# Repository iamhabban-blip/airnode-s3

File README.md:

# AirNode S3 — ESP32-S3 Environmental Sensor Node

A compact, USB-C powered Wi-Fi/BLE sensor board: ESP32-S3 module, Bosch BME280 (temperature / humidity / pressure), a Qwiic/STEMMA-QT port for more I2C sensors, a UART debug header and a 6-GPIO breakout.

Designed in **KiCad 7** as a native, self-contained project (local symbol, footprint and 3D libraries), with fabrication and assembly data ready for JLCPCB-class manufacturing.

**Status:** design complete and verified (ERC + DRC clean). Not yet fabricated.

| | |
|---|---|
| Board | 44 × 54 mm, 2 layers, 1.6 mm FR-4, 1 oz copper, 2 mm corner radius |
| Parts | 27 placed (SMD except the two pin headers and the USB-C shell legs), 4 × M2.5 mounting holes |
| Routing | 245 track segments, 120 vias, 0 unrouted |
| Rules | 0.2 mm track/space, 0.6/0.3 mm vias, 0.3 mm copper-to-edge |
| ERC | 0 errors, 0 warnings (1 reviewed exclusion, see below) |
| DRC | 0 violations, 0 unconnected, 0 footprint errors |

| Board render (top / bottom) | KiCad PCB editor |
|---|---|
|  |  |

---

## Schematic

Single A3 sheet, grouped into functional blocks (USB-C input, LDO, MCU, reset/boot, LEDs, sensor/I2C, debug/GPIO). Full PDF: [`docs/airnode-schematic.pdf`](docs/airnode-schematic.pdf).

---

## Design decisions

### 1. Power input and protection
- **USB-C sink, USB 2.0 only.** 5.1 kΩ pull-downs on CC1/CC2 (R1, R2) make the board a standard sink, so any USB-C charger or port supplies 5 V. No PD controller is needed at this power level.
- **Both D+/D− pairs connected** (A6/B6, A7/B7), so the plug works in either orientation.
- **F1, 500 mA PTC fuse** on VBUS protects the host port and the cable from a board-level short.
- **U3, USBLC6-2SC6 TVS array** sits directly behind the connector and clamps ESD on D+/D− and VBUS before it can reach the ESP32. It is placed as a flow-through (rotated 270°) so the data lines pass straight under it without stubs.

### 2. 3.3 V regulation
- **U2, AP2112K-3.3 LDO:** 600 mA output and 250 mV dropout. Wi-Fi TX bursts on the ESP32-S3 peak at roughly 350 mA, which leaves about 40 % headroom.
- An LDO was chosen over a buck converter: at 5 V in and about 100 mA average, dissipation is around 0.17 W. That is well within SOT-23-5 limits, avoids switching noise near the sensor and antenna, and costs fewer parts.
- **Capacitors:** 10 µF on the input (C1) and output (C2), then 10 µF + 100 nF (C3, C4) at the module's 3V3 pin for Wi-Fi burst current.

### 3. MCU
- **ESP32-S3-WROOM-1-N8** (8 MB flash, PCB antenna, pre-certified module).
- **Native USB** on GPIO19/20 handles both flashing and serial (CDC), so there is no USB-UART bridge chip. That saves cost, area and a failure point.
- **EN:** 10 kΩ + 1 µF RC (R3, C5) delays enable until 3V3 is stable, the reset condition Espressif recommends.
- **Strapping:** BOOT (IO0) has a 10 kΩ pull-up with a button to ground for download mode. RESET is a button on EN.
- **LEDs:** a power LED (green) and a GPIO2 status LED (blue), each with 1 kΩ (about 1.3 mA, enough for an indicator).

### 4. Sensor and I2C
- **BME280 in I2C mode:** CSB is tied high, and SDO is tied low for address 0x76.
- **I2C pull-ups:** 4.7 kΩ on SDA (IO8) and SCL (IO9), shared with the Qwiic connector in standard Qwiic pinout (GND, 3V3, SDA, SCL).
- **Thermal placement.** A board-mounted humidity/temperature sensor reads high if it sits next to heat sources. The BME280 is in the opposite bottom corner from the LDO and well below the ESP32 module.

### 5. Layout
- **Antenna.** The module sits at the top edge with its antenna flush to the board edge. The footprint's keep-out (no copper, tracks, vias or parts on either layer) covers the full width under and beside the antenna, following Espressif's guidance for a PCB-antenna module.
- **Ground strategy.** Both layers are poured with GND. The bottom layer is kept as close to a solid plane as possible: signals use it only to cross, and every SMD ground pad gets its own via to that plane. 53 stitching vias tie the two pours together on a 3 mm grid outside component courtyards.
- **USB routing.** D+ and D− run on the top layer with **zero vias** over the unbroken bottom ground plane, 29.6 mm and 30.4 mm long. At USB Full Speed (12 Mbit/s) a 0.8 mm mismatch is irrelevant; the priorities were short, via-free, referenced to ground and close-coupled.
- **USB-C pad escape.** On 16-pin USB-C the D+/D− pads interleave (D−, D+, D−, D+), so the two pairs can't both leave the pad row on one layer. D+ (A6↔B6) is joined by a short loop under the pad row and D− (B7↔A7) by a bridge above it, so both pairs exit cleanly with no vias.
- **Track widths by netclass:**
  - VBUS / VBUS_IN: 0.4 mm
  - +3V3 / GND: 0.3 mm
  - signals and USB: 0.2 mm (USB at 0.2 mm to fit the 0.5 mm-pitch connector pads)
- **Pad connections.** SMD pads connect to the pours solidly (better for reflow); through-hole pads use thermal reliefs (better for hand soldering).

*Top: the antenna keep-out band runs across the top edge, with ground pour and stitching vias everywhere else. Bottom: a near-solid ground plane under the USB and signal routing, plus header pin legends.*

### 6. Manufacturability (DFM)
- **ESP32 thermal vias opened from 0.2 to 0.3 mm.** Espressif's footprint uses 0.2 mm vias under the module's ground pad. The project's local copy uses 0.3 mm, JLCPCB's standard 2-layer minimum, so the board needs no advanced-process surcharge.
- **USB-C peg clearance.** In the GCT USB4105 land pattern, the connector's alignment-peg holes sit 0.19 mm from its outer ground pads. That is the manufacturer's geometry, so a scoped DRC rule (`airnode.kicad_dru`) relaxes hole clearance **for J1 only** rather than loosening the board-wide rule.
- **Silkscreen.**
  - Every legend stays off pads and inside the board edge.
  - Header pin names are on the bottom silkscreen, readable when the board is flipped to wire it.
  - The module's antenna-end silkscreen is pulled 0.5 mm inside its outline so it never crosses the board edge.
- **Assembly files.**
  - The BOM groups parts and lists manufacturer part numbers.
  - The pick-and-place (CPL) file is in JLCPCB's format.
  - Mounting holes are excluded from both.

### 7. Verification
- **ERC:** run in the KiCad 7 schematic editor.
  - 0 errors.
  - One warning reviewed and excluded: *"Bidirectional pin connected to power output"* on the BME280's SDO. SDO is deliberately strapped to GND to select address 0x76, and the GND net carries a PWR_FLAG, so this is a false positive by design.
- **DRC:** KiCad 7 DRC with all track errors reported. 0 violations, 0 unconnected pads, 0 footprint/library mismatches.
- **Netlist audit:** the exported netlist was compared pin by pin against the design intent (23 nets) and matches exactly.

Reports: [`docs/airnode-erc.rpt`](docs/airnode-erc.rpt) · [`docs/airnode-drc.rpt`](docs/airnode-drc.rpt)

---

## Files

| Path | Contents |
|---|---|
| `airnode.kicad_pro / .kicad_sch / .kicad_pcb` | KiCad 7 project, schematic, board |
| `airnode.kicad_sym`, `airnode.pretty/`, `airnode.3dshapes/` | Project-local symbol, footprint and 3D-model libraries (opens on any machine) |
| `sym-lib-table`, `fp-lib-table`, `airnode.kicad_dru` | Library tables and the scoped custom DRC rule |
| `fab/airnode-gerbers.zip` | Gerbers + Excellon drill + drill map, ready to upload |
| `fab/airnode-bom.csv`, `fab/airnode-cpl.csv` | Assembly BOM and pick-and-place (JLCPCB format) |
| `fab/airnode.step` | Full 3D STEP model for mechanical / enclosure work |
| `docs/` | Schematic PDF, assembly drawing, layout PDF, ERC and DRC reports, netlist |
| `images/` | Renders and KiCad screenshots |

## Ordering
1. Upload `fab/airnode-gerbers.zip` and keep the defaults: 2 layers, 1.6 mm, HASL or ENIG.
2. For assembly, upload `airnode-bom.csv` and `airnode-cpl.csv`, then match each line to the fab's parts catalogue. Generic resistors, capacitors and LEDs can use any equivalent 0603/0805 part.
3. Check part rotations in the assembler's preview before confirming. Rotation conventions differ between libraries.

## Not included / next revision
- The KiCad 7 library has no 3D model for the JST-SH Qwiic connector, so it appears as bare pads in the 3D view.
- **Possible rev B:**
  - battery input with a charger (TP4056 or MCP73831) and power-path switching
  - a deep-sleep current-measurement jumper
  - a thermal slot around the BME280

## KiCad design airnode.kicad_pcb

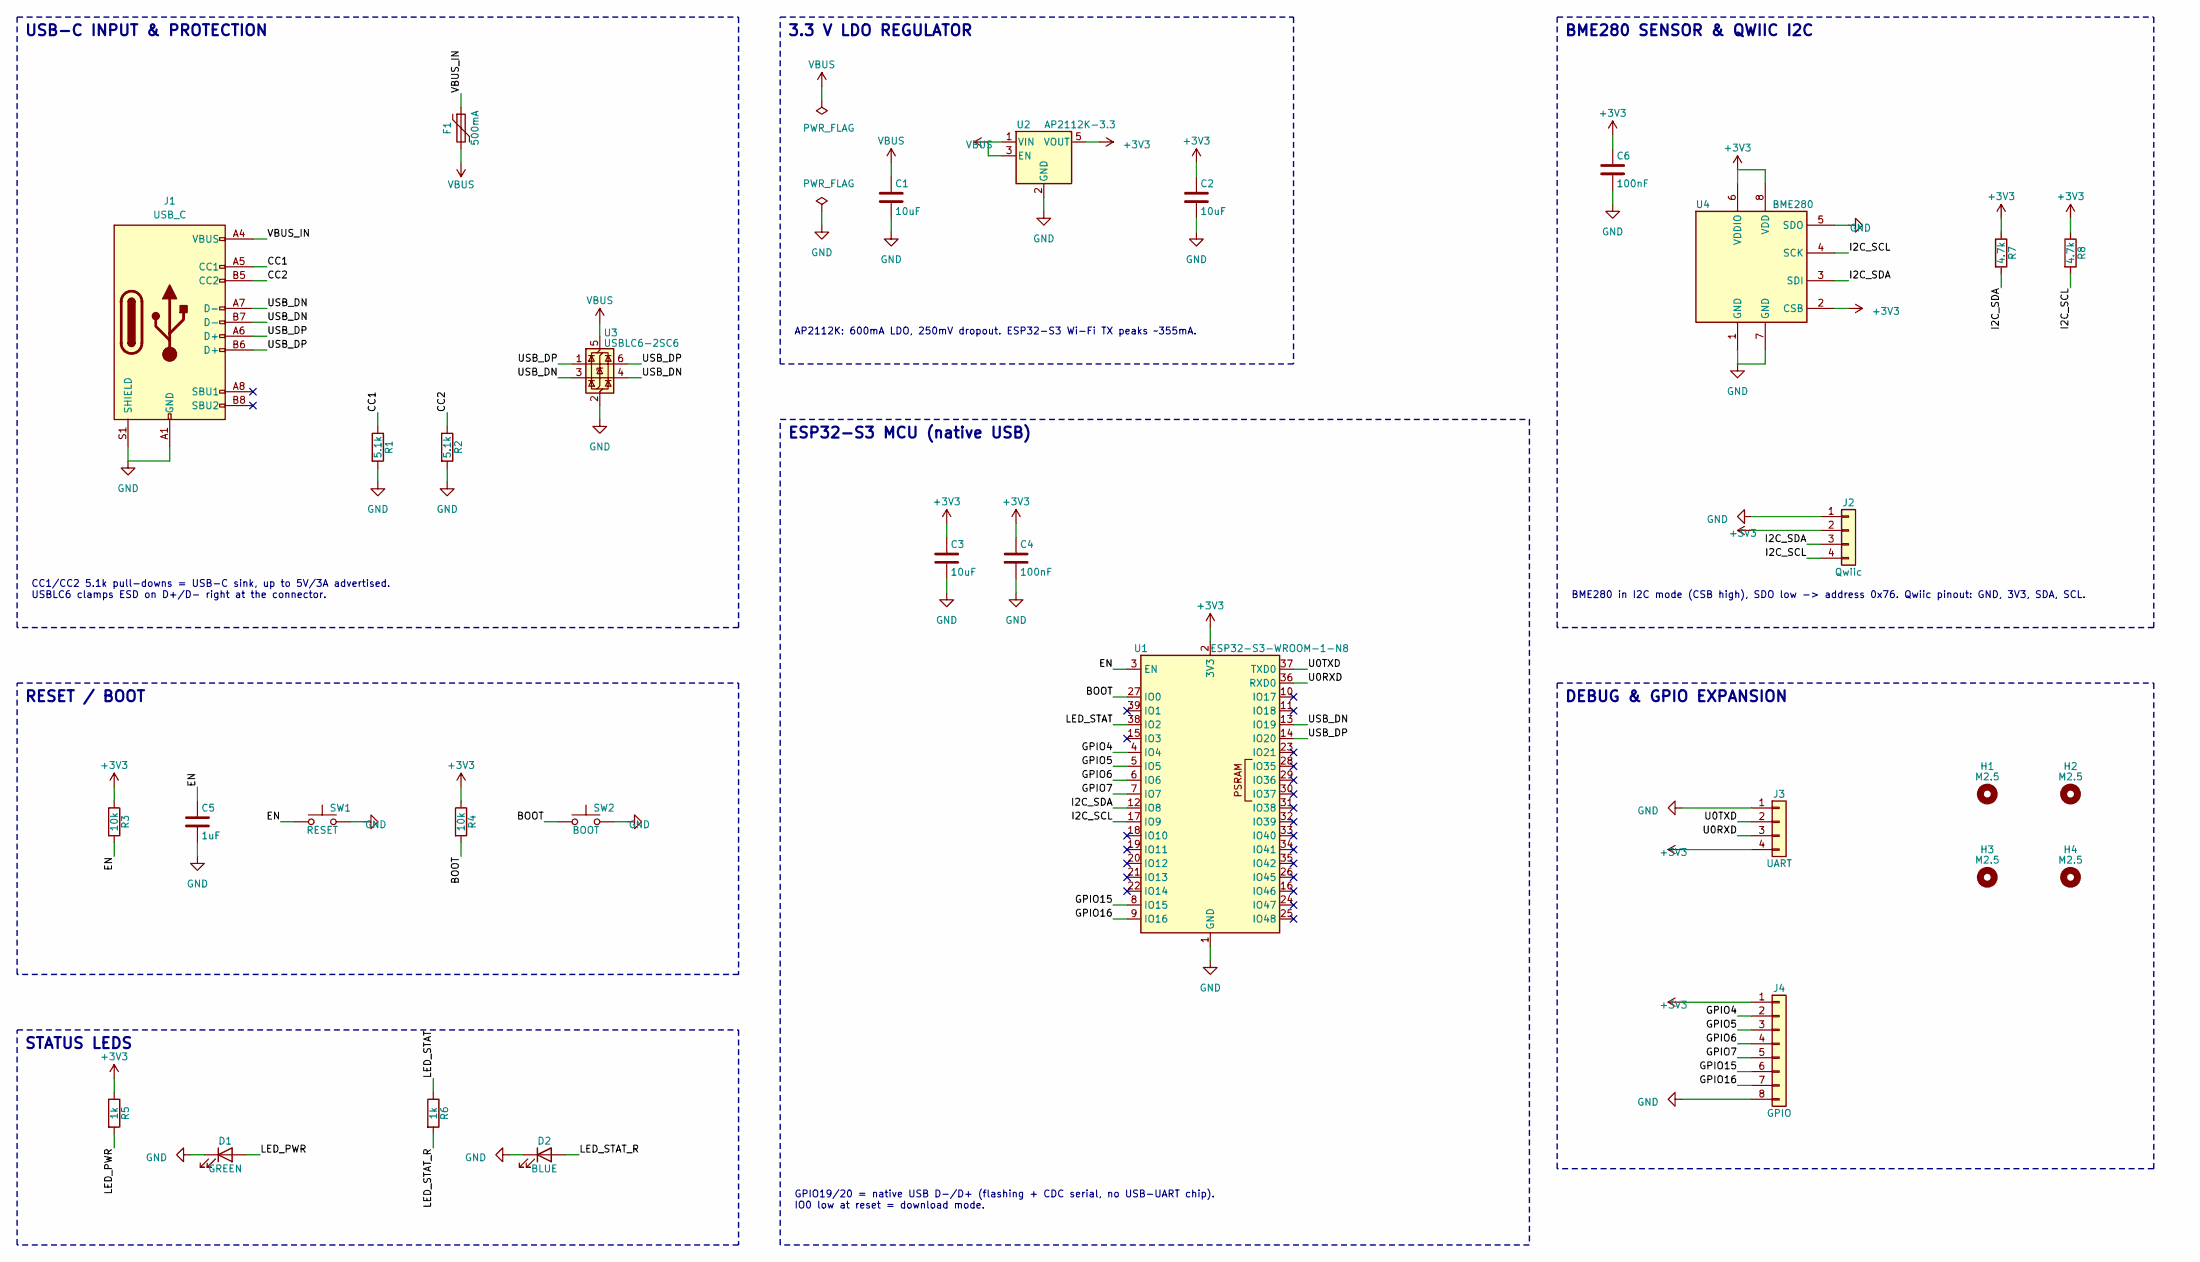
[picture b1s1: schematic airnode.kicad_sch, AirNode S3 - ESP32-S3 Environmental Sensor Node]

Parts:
C1, C2, C3: 10uF; C_0805_2012Metric
C4, C6: 100nF; C_0603_1608Metric
C5: 1uF; C_0603_1608Metric
D1: GREEN; LED_0603_1608Metric
D2: BLUE; LED_0603_1608Metric
F1: 500mA; Fuse_1206_3216Metric; MPN Littelfuse 1206L050YR
H1, H2, H3, H4: M2.5; MountingHole_2.7mm_M2.5
J1: USB_C; USB_C_Receptacle_GCT_USB4105-xx-A_16P_TopMnt_Horizontal; MPN GCT USB4105-GF-A
J2: Qwiic; JST_SH_SM04B-SRSS-TB_1x04-1MP_P1.00mm_Horizontal; MPN JST SM04B-SRSS-TB
J3: UART; PinHeader_1x04_P2.54mm_Vertical
J4: GPIO; PinHeader_1x08_P2.54mm_Vertical
R1, R2: 5.1k; R_0603_1608Metric
R3, R4: 10k; R_0603_1608Metric
R5, R6: 1k; R_0603_1608Metric
R7, R8: 4.7k; R_0603_1608Metric
SW1: RESET; SW_SPST_TL3342; MPN E-Switch TL3342F160QG
SW2: BOOT; SW_SPST_TL3342; MPN E-Switch TL3342F160QG
U1: ESP32-S3-WROOM-1-N8; ESP32-S3-WROOM-1; MPN Espressif ESP32-S3-WROOM-1-N8
U2: AP2112K-3.3; SOT-23-5; MPN Diodes AP2112K-3.3TRG1
U3: USBLC6-2SC6; SOT-23-6; MPN ST USBLC6-2SC6
U4: BME280; Bosch_LGA-8_2.5x2.5mm_P0.65mm_ClockwisePinNumbering; MPN Bosch BME280

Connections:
+3V3: C2.1, C3.1, C4.1, C6.1, J2.2, J3.4, J4.1, R3.1, R4.1, R5.1, R7.1, R8.1, U1.2 (3V3), U2.5 (VOUT), U4.2 (CSB), U4.6 (VDDIO), U4.8 (VDD)
BOOT: R4.2, SW2.1, U1.27 (IO0)
CC1: J1.A5 (CC1), R1.1
CC2: J1.B5 (CC2), R2.1
EN: C5.1, R3.2, SW1.1, U1.3 (EN)
GND: C1.2, C2.2, C3.2, C4.2, C5.2, C6.2, D1.1 (K), D2.1 (K), J1.A1 (GND), J1.A12 (GND), J1.B1 (GND), J1.B12 (GND), J1.S1 (SHIELD), J2.1, J3.1, J4.8, R1.2, R2.2, SW1.2, SW2.2, U1.1 (GND), U1.40 (GND), U1.41 (GND), U2.2 (GND), U3.2 (GND), U4.1 (GND), U4.5 (SDO), U4.7 (GND)
GPIO4: J4.2, U1.4 (IO4)
GPIO5: J4.3, U1.5 (IO5)
GPIO6: J4.4, U1.6 (IO6)
GPIO7: J4.5, U1.7 (IO7)
GPIO15: J4.6, U1.8 (IO15)
GPIO16: J4.7, U1.9 (IO16)
I2C_SCL: J2.4, R8.2, U1.17 (IO9), U4.4 (SCK)
I2C_SDA: J2.3, R7.2, U1.12 (IO8), U4.3 (SDI)
LED_PWR: D1.2 (A), R5.2
LED_STAT: R6.1, U1.38 (IO2)
LED_STAT_R: D2.2 (A), R6.2
U0RXD: J3.3, U1.36 (RXD0)
U0TXD: J3.2, U1.37 (TXD0)
USB_DN: J1.A7 (D-), J1.B7 (D-), U1.13 (IO19), U3.3 (I/O2), U3.4 (I/O2)
USB_DP: J1.A6 (D+), J1.B6 (D+), U1.14 (IO20), U3.1 (I/O1), U3.6 (I/O1)
VBUS: C1.1, F1.2, U2.1 (VIN), U2.3 (EN), U3.5 (VBUS)
VBUS_IN: F1.1, J1.A4 (VBUS), J1.A9 (VBUS), J1.B4 (VBUS), J1.B9 (VBUS)

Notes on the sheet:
ESP32-S3 MCU (native USB)
BME280 in I2C mode (CSB high), SDO low -> address 0x76. Qwiic pinout: GND, 3V3, SDA, SCL.
GPIO19/20 = native USB D-/D+ (flashing + CDC serial, no USB-UART chip). IO0 low at reset = download mode.
STATUS LEDS
CC1/CC2 5.1k pull-downs = USB-C sink, up to 5V/3A advertised. USBLC6 clamps ESD on D+/D- right at the connector.
3.3 V LDO REGULATOR
AP2112K: 600mA LDO, 250mV dropout. ESP32-S3 Wi-Fi TX peaks ~355mA.
RESET / BOOT
DEBUG & GPIO EXPANSION
BME280 SENSOR & QWIIC I2C
USB-C INPUT & PROTECTION

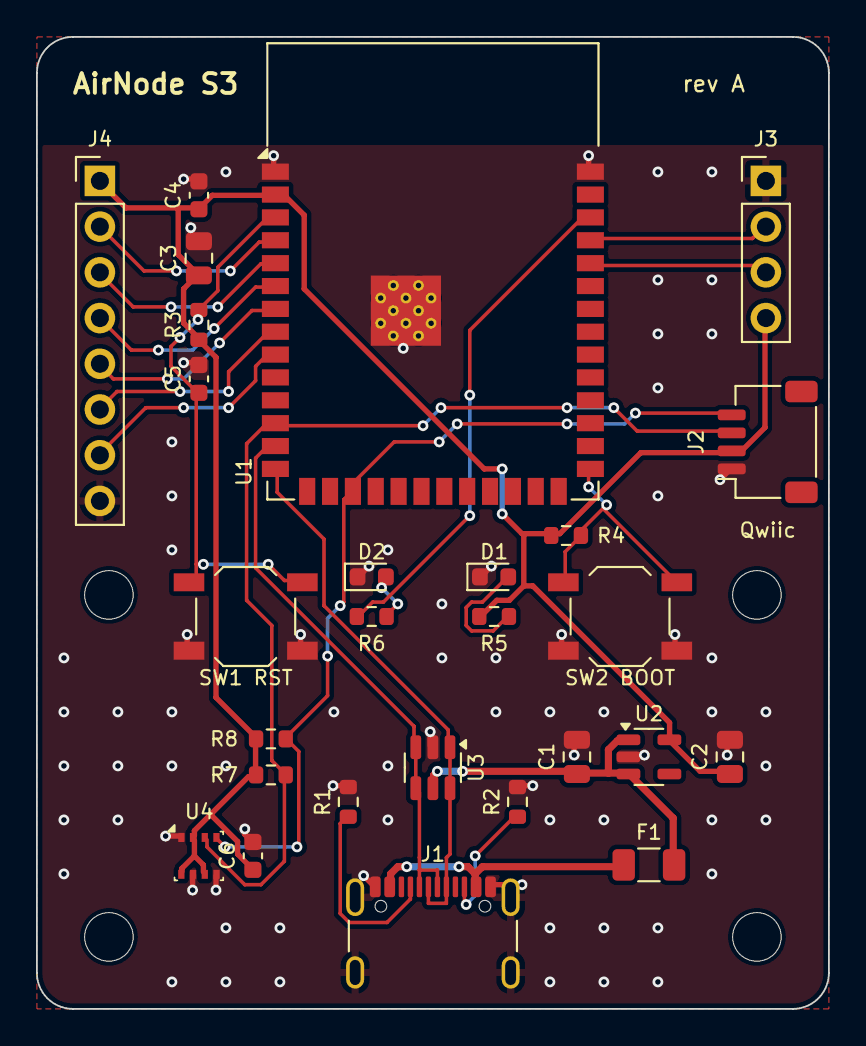
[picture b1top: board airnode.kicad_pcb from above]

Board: 2 copper layers, 44.0 x 54.0 mm, 31 parts (0 on the bottom side), 23 nets.

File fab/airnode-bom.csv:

Comment,Designator,Footprint,Manufacturer Part,Quantity,LCSC Part #
USB_C,J1,USB_C_Receptacle_GCT_USB4105-xx-A_16P_TopMnt_Horizontal,GCT USB4105-GF-A,1,
5.1k,"R1,R2",R_0603_1608Metric,,2,
500mA,F1,Fuse_1206_3216Metric,Littelfuse 1206L050YR,1,
USBLC6-2SC6,U3,SOT-23-6,ST USBLC6-2SC6,1,
AP2112K-3.3,U2,SOT-23-5,Diodes AP2112K-3.3TRG1,1,
10uF,"C1,C2,C3",C_0805_2012Metric,,3,
ESP32-S3-WROOM-1-N8,U1,ESP32-S3-WROOM-1,Espressif ESP32-S3-WROOM-1-N8,1,
100nF,"C4,C6",C_0603_1608Metric,,2,
10k,"R3,R4",R_0603_1608Metric,,2,
1uF,C5,C_0603_1608Metric,,1,
RESET,SW1,SW_SPST_TL3342,E-Switch TL3342F160QG,1,
BOOT,SW2,SW_SPST_TL3342,E-Switch TL3342F160QG,1,
1k,"R5,R6",R_0603_1608Metric,,2,
GREEN,D1,LED_0603_1608Metric,,1,
BLUE,D2,LED_0603_1608Metric,,1,
BME280,U4,Bosch_LGA-8_2.5x2.5mm_P0.65mm_ClockwisePinNumbering,Bosch BME280,1,
4.7k,"R7,R8",R_0603_1608Metric,,2,
Qwiic,J2,JST_SH_SM04B-SRSS-TB_1x04-1MP_P1.00mm_Horizontal,JST SM04B-SRSS-TB,1,
UART,J3,PinHeader_1x04_P2.54mm_Vertical,,1,
GPIO,J4,PinHeader_1x08_P2.54mm_Vertical,,1,
